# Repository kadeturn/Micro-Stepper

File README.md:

# Micro Stepper

This repository contains work on various breakout boards for the micro linear stepper motors used in motorised mobile phone cameras.

These stepper motors are available in several variations from different Chinese suppliers.

Current and future CAD models for the stepper motors can be found [here](hw/cad).

All PCBs are created using KiCad Nightly builds.

---

## Micro Breakout

The first breakout board is based on [this](https://www.aliexpress.com/item/4000616045699.html?spm=a2g0s.12269583.0.0.51854815RwJf8O) stepper motor from Aliexpress.

Both the Model A and Model B variants work with this breakout (the only difference being their linear guide mounting features).
These motors can produce a force in the range of ~100-150gf, the main downside is that they have quite a bit of backlash.

The breakout uses the [Trinamic TMC2300](https://www.trinamic.com/products/integrated-circuits/details/tmc2300-la/) low voltage stepper motor driver. 

Both step/direction and UART based control are possible, with the latter enabling current sensing (useful for end stop detection).

The UART is single wire based, so an additional external resistor is required to split TX & RX out separately (more to come on that later).

KiCad and Gerber files are located [here](hw/micro_breakout_001).

---

## Micro Driver

The World's smallest stepper driver board (probably).

Based on the same TMC2300 stepper motor driver as used in the Micro Breakout. It's designed for use with any small low voltage stepper motor.

**The PCB is just 10.2mm x 6mm!!**

Due to a small issue with the enable pin always pulled low, and incorrect silkscreen, the files are currently not released (wait for rev002).

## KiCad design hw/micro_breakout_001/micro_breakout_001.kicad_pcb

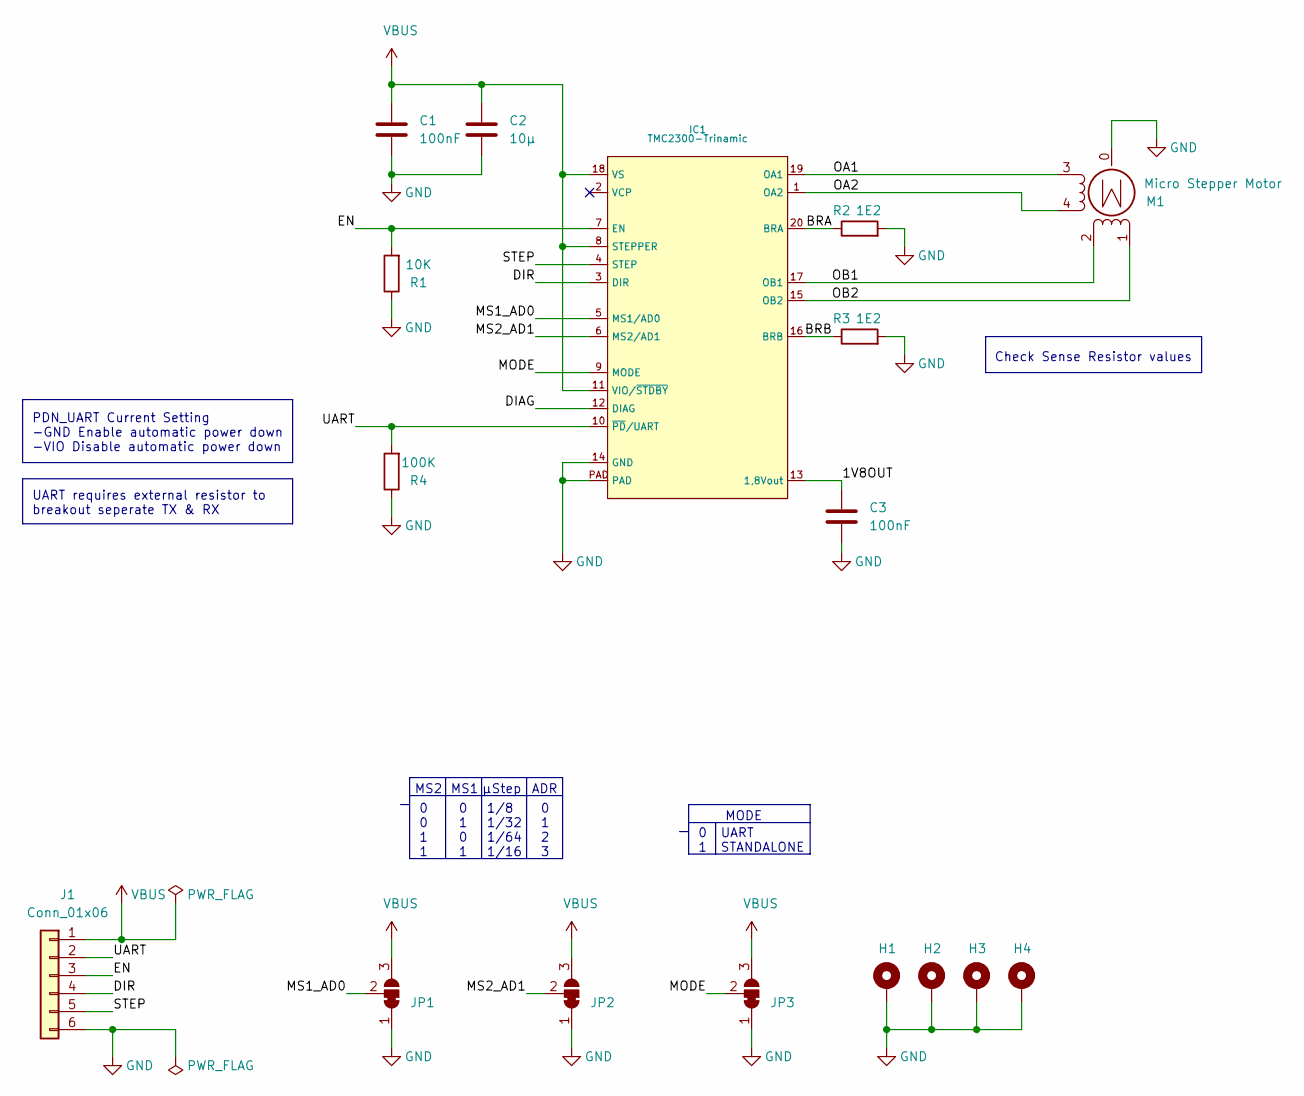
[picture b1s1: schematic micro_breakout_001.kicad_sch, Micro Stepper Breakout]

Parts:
C1, C3: 100nF; C_0402_1005Metric
C2: 10µ; C_0603_1608Metric
H1, H2, H3, H4: MountingHole; Mounting_Wuerth_WA-SMSI-M1.6_H1mm_9774010633
IC1: TMC2300-Trinamic; QFN20
J1: Conn_01x06; JST_SH_SM06B-SRSS-TB_1x06-1MP_P1.00mm_Horizontal
JP1, JP2, JP3: SolderJumper_3_Bridged12; J_NCNO_0903_20
M1: Micro Stepper Motor; Micro_Stepper
R1: 10K; R_0402_1005Metric
R2, R3: 1E2; R_0402_1005Metric
R4: 100K; R_0402_1005Metric

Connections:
/1V8OUT: C3.1, IC1.13 (1,8Vout)
/BRA: IC1.20 (BRA), R2.1
/BRB: IC1.16 (BRB), R3.1
/DIAG: IC1.12 (DIAG)
/DIR: IC1.3 (DIR), J1.4
/EN: IC1.7 (EN), J1.3, R1.2
/MODE: IC1.9 (MODE), JP3.2 (C)
/MS1_AD0: IC1.5 (MS1/AD0), JP1.2 (C)
/MS2_AD1: IC1.6 (MS2/AD1), JP2.2 (C)
/OA1: IC1.19 (OA1), M1.3
/OA2: IC1.1 (OA2), M1.4
/OB1: IC1.17 (OB1), M1.2 (-)
/OB2: IC1.15 (OB2), M1.1
/STEP: IC1.4 (STEP), J1.5
/UART: IC1.10 (~PD~/UART), J1.2, R4.2
GND: C1.2, C2.2, C3.2, H1.1, H2.1, H3.1, H4.1, IC1.14 (GND), IC1.PAD, J1.6, JP1.1 (A), JP2.1 (A), JP3.1 (A), M1.0 (Sheild), R1.1, R2.2, R3.2, R4.1
VBUS: C1.1, C2.1, IC1.8 (STEPPER), IC1.11 (VIO/~STDBY), IC1.18 (VS), J1.1, JP1.3 (B), JP2.3 (B), JP3.3 (B)

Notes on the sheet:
PDN_UART Current Setting -GND Enable automatic power down -VIO Disable automatic power down
UART requires external resistor to breakout seperate TX & RX
MS2
0 0 1 1
MS1
0 1 0 1
µStep
1/8 1/32 1/64 1/16
ADR
0 1 2 3
0 1
UART STANDALONE
MODE
Check Sense Resistor values

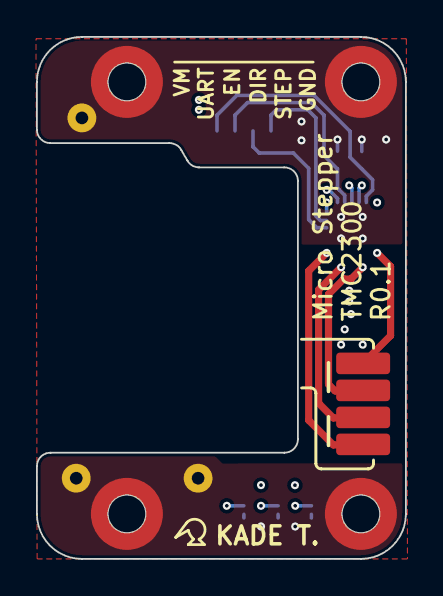
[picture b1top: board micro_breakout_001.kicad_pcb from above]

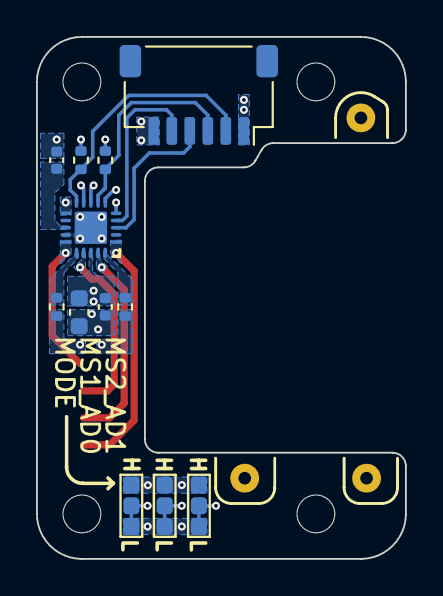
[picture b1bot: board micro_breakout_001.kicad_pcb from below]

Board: 4 copper layers, 20.5 x 29.0 mm, 17 parts (13 on the bottom side), 16 nets.

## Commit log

2021-02-17 Add license
2021-02-17 Commit stepper motor CAD model
2021-02-17 Add Micro Breakout KiCad files
2021-02-17 Picture sizes updated
2021-02-18 Update README.md Add micro driver finger picture
    Update README.md
    Readme updated
    Readme updated
